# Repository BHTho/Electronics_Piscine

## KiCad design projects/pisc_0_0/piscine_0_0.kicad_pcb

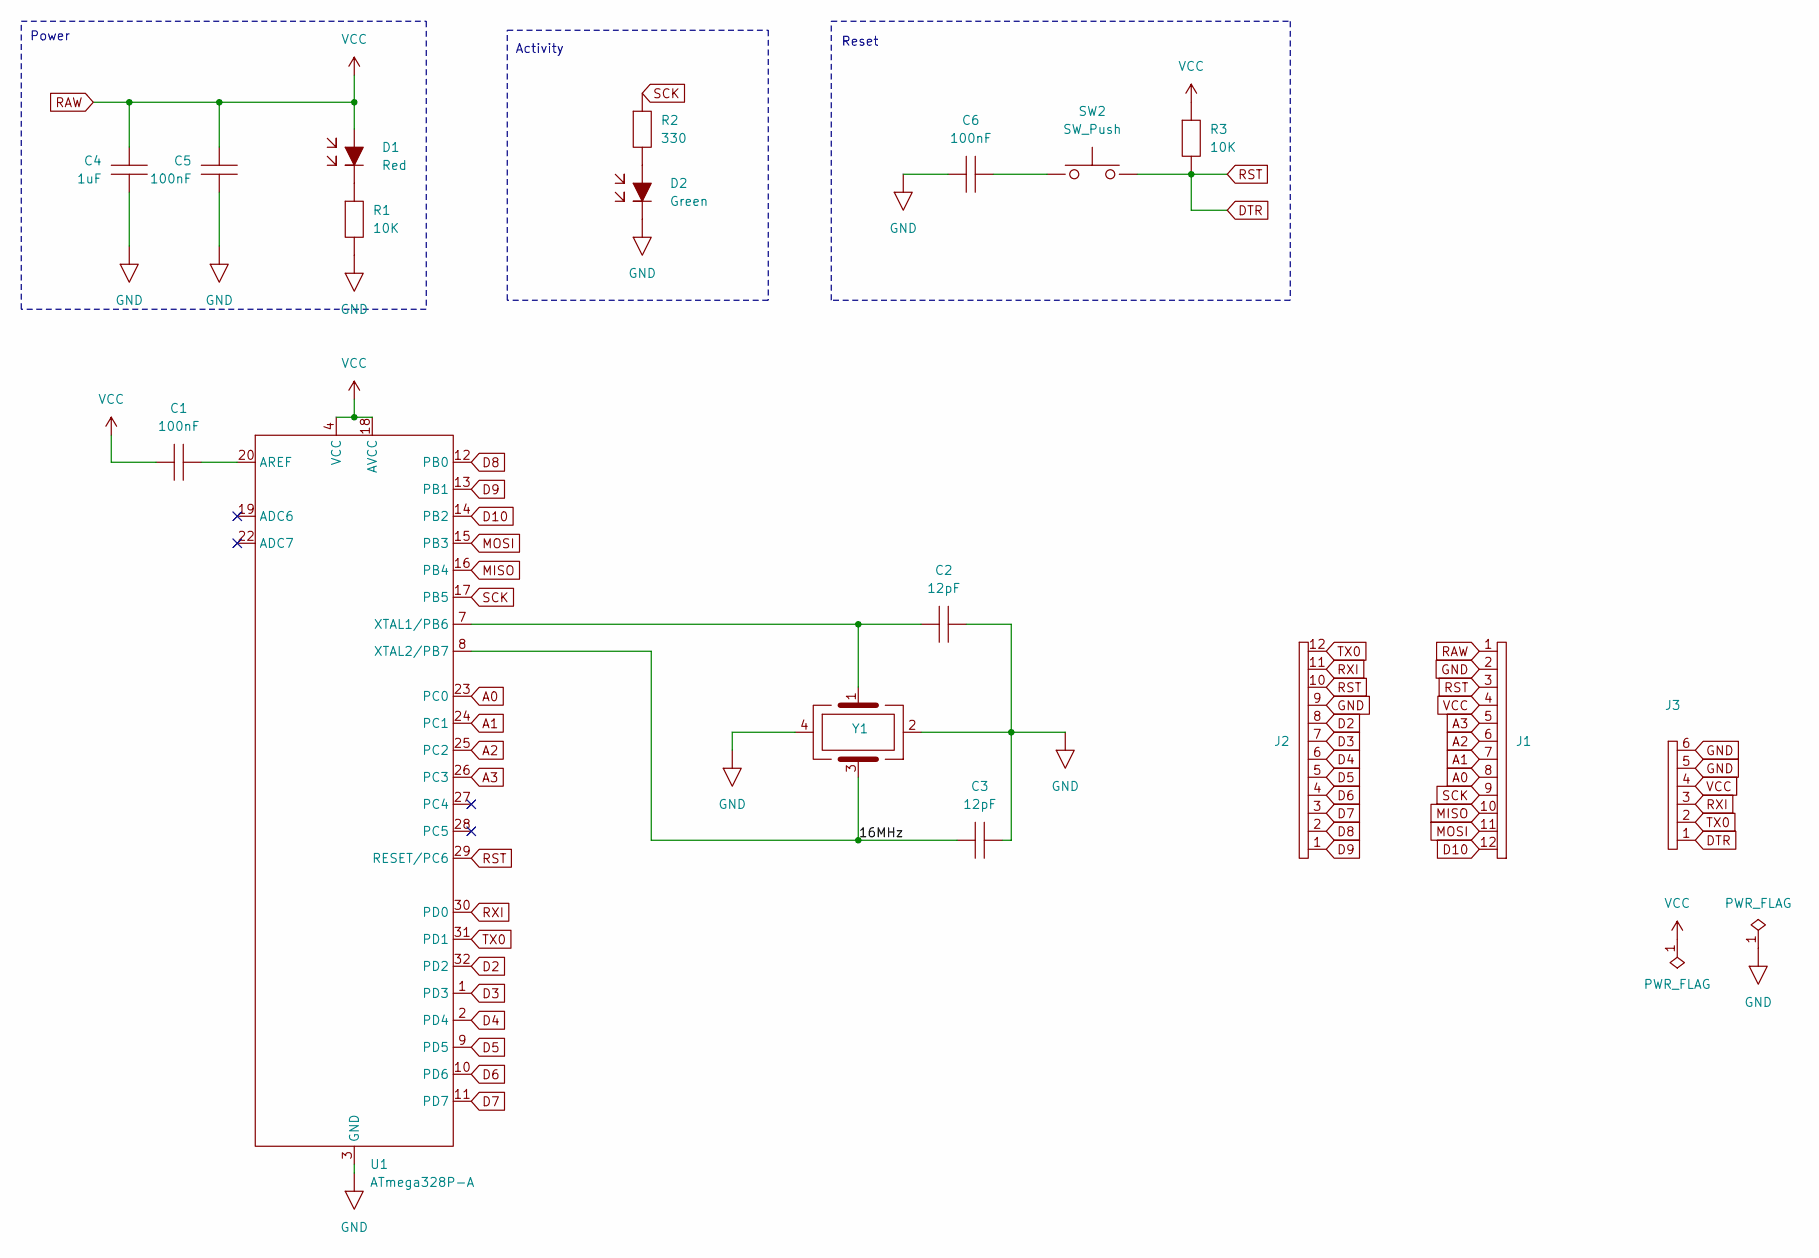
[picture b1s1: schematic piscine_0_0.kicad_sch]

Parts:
C1, C5, C6: 100nF; 0603
C2, C3: 12pF; 0603
C4: 1uF; 0603
D1: Red; 0603
D2: Green; 0603
J1, J2: 12pin_gpio
J3: 6pin_gpio
R1, R3: 10K; 0603
R2: 330; 0603
SW2: SW_Push; TS_3225
U1: ATmega328P-A; ATMEGA328P-AU
Y1: crys_osc_smd3225_4

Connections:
/16MHz: C3.1, U1.8 (XTAL2/PB7), Y1.3
A0: J1.8, U1.23 (PC0)
A1: J1.7, U1.24 (PC1)
A2: J1.6, U1.25 (PC2)
A3: J1.5, U1.26 (PC3)
D2: J2.8, U1.32 (PD2)
D3: J2.7, U1.1 (PD3)
D4: J2.6, U1.2 (PD4)
D5: J2.5, U1.9 (PD5)
D6: J2.4, U1.10 (PD6)
D7: J2.3, U1.11 (PD7)
D8: J2.2, U1.12 (PB0)
D9: J2.1, U1.13 (PB1)
D10: J1.12, U1.14 (PB2)
DTR: J1.3, J2.10, J3.1, R3.2, SW2.2, U1.29 (RESET/PC6)
GND: C2.2, C3.2, C4.2, C5.2, C6.2, D2.1, J1.2, J2.9, J3.5, J3.6, R1.2, U1.3 (GND), Y1.2, Y1.4
MISO: J1.10, U1.16 (PB4)
MOSI: J1.11, U1.15 (PB3)
unnamed: C6.1, SW2.1
unnamed: D1.1, R1.1
unnamed: D2.2, R2.2
unnamed: C1.1, U1.20 (AREF)
unnamed: C2.1, U1.7 (XTAL1/PB6), Y1.1
RAW: C1.2, C4.1, C5.1, D1.2, J1.1, J1.4, J3.4, R3.1, U1.4 (VCC), U1.18 (AVCC)
RXI: J2.11, J3.3, U1.30 (PD0)
SCK: J1.9, R2.1, U1.17 (PB5)
TX0: J2.12, J3.2, U1.31 (PD1)

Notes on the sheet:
Activity
Reset
Power

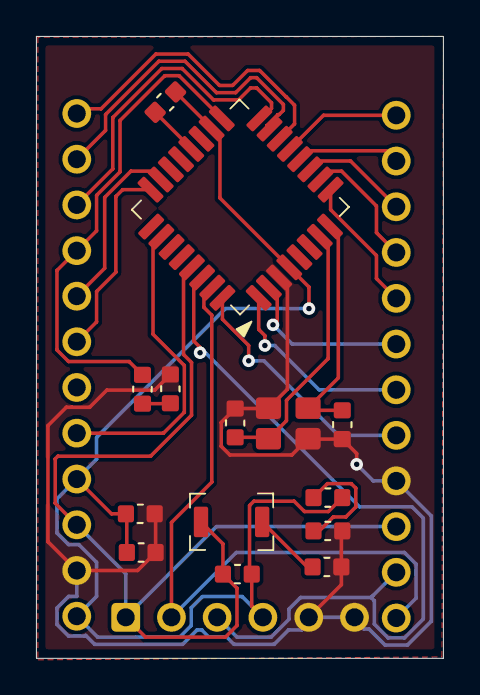
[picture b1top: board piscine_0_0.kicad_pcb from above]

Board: 2 copper layers, 22.6 x 34.5 mm, 17 parts (0 on the bottom side), 26 nets.

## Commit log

2025-11-17 first commit
    added custom symbols
2025-11-17 finished first draft of schematic 70 errors :(
2025-11-18 updated symbols with correct pins
2025-11-18 added target schema
2025-11-19 testing file perms
2025-11-19 added power_flag to schematic for gnd and vcc
    edited gpio symbols to use passive pins
    edited quartz crystal to use power input pins for 2 and 4
2025-11-19 computer cashing, need to save
2025-11-19 replaced a gnd flag with vcc
2025-11-19 added through-hole footprints updated symbols with link to their footprints updated schematic symbols adding backups
2025-11-20 Created function but ugly pcb design for arduino mini pcb design is traced with 0 errors updated schematic to include missing gpio footprints
2025-11-20 created electric wizard silkscreen art
2025-11-20 added wizard silk-screen to pcb
2025-11-26 added ground plane to pcb
2025-11-26 added schematic pdf
2025-11-26 added pcb pdf
2025-11-26 added photos of soldered boards
2025-11-26 added readme for design
2025-11-26 added project readmes
2025-11-26 moved photos to dir and added new photos
2025-11-26 removed junk files
2025-11-26 replaced schema file
